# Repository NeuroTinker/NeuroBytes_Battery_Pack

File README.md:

# NeuroBytes Battery Pack

The NeuroBytes Battery Pack provides power to NeuroBytes products, open-source hardware neuron simulators designed and sold by [NeuroTinker, LLC](http://www.neurotinker.com/). Battery Packs feature a pair of power connections and a power switch with indicator LED, and require four alkaline AA batteries to operate.

These boards were designed in KiCad and Inkscape and are released under the terms of the Creative Commons Attribution-ShareAlike 4.0 license, available here: https://creativecommons.org/licenses/by-sa/4.0/. The NeuroBytes Battery Pack is Certified Open Source Hardware as defined by [OSHWA](https://www.oshwa.org), certification number US000114.

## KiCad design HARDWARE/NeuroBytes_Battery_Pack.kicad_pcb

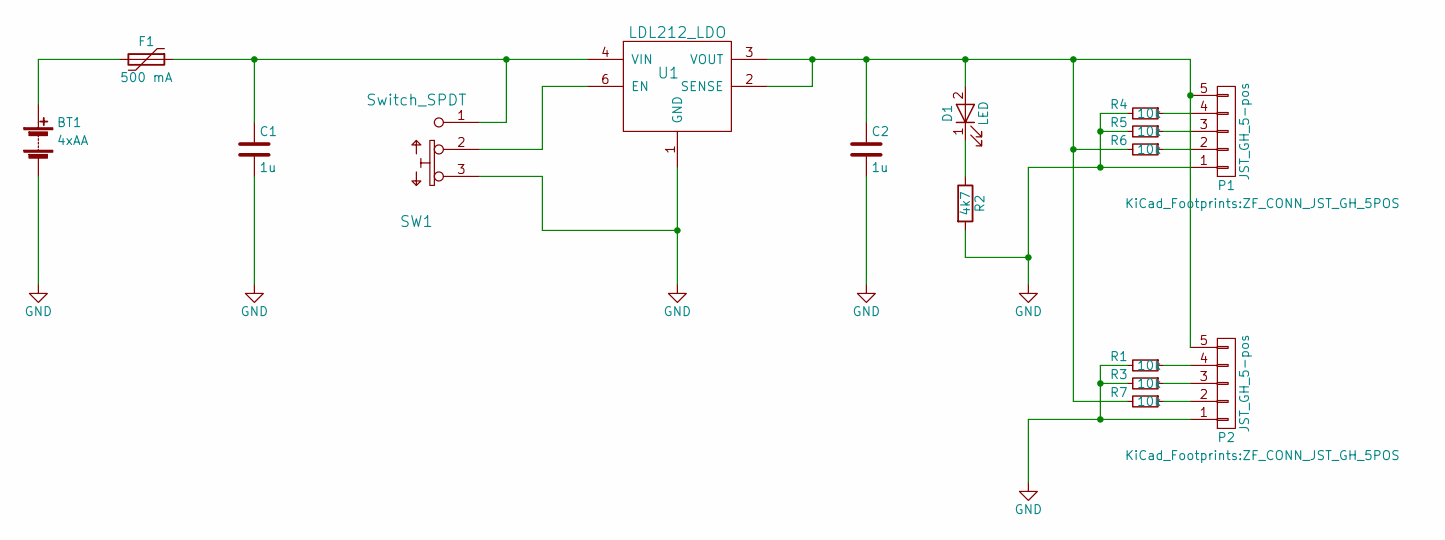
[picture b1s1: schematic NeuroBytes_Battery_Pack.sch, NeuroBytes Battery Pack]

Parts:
BT1: 4xAA; ZF_BATT_4xAA_BC4AAPC; Mfr Part # BC4AAPC
C1, C2: 1u; C_0603_HandSoldering; Mfr Part # LMK107B7105KA-T
D1: LED; ZF_SMD_NonPol_0402; Mfr Part # SMLP13EC8TT86
F1: 500 mA; ZF_SMD_nonpol_1210; Mfr Part # 0ZCH0050FF2G
P1, P2: JST_GH_5-pos; ZF_CONN_JST_GH_5POS; Mfr Part # SM05B-GHS-TB(LF)(SN)
R1, R3, R4, R5, R6, R7: 10k; ZF_SMD_NonPol_0402; Mfr Part # RC0402FR-0710KL
R2: 4k7; ZF_SMD_NonPol_0402; Mfr Part # RC0402FR-074K7L
SW1: Switch_SPDT; ZF_SW_PCM12SMTR; Mfr Part # PCM12SMTR
U1: LDL212_LDO; ZF_IC_DFN6_3x3; Mfr Part # LDL212PU50R

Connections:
GND: BT1.2 (-), C1.2, C2.2, P1.1, P2.1, R1.2, R2.2, R3.2, R4.2, R5.2, SW1.3, U1.1 (GND)
unnamed: BT1.1 (+), F1.2
unnamed: C1.1, F1.1, SW1.1, U1.4 (VIN)
unnamed: C2.1, D1.2 (A), P1.5, P2.5, R6.2, R7.2, U1.2 (SENSE), U1.3 (VOUT)
unnamed: D1.1 (K), R2.1
unnamed: P1.2, R6.1
unnamed: P1.3, R5.1
unnamed: P1.4, R4.1
unnamed: P2.2, R7.1
unnamed: P2.3, R3.1
unnamed: P2.4, R1.1
unnamed: SW1.2, U1.6 (EN)

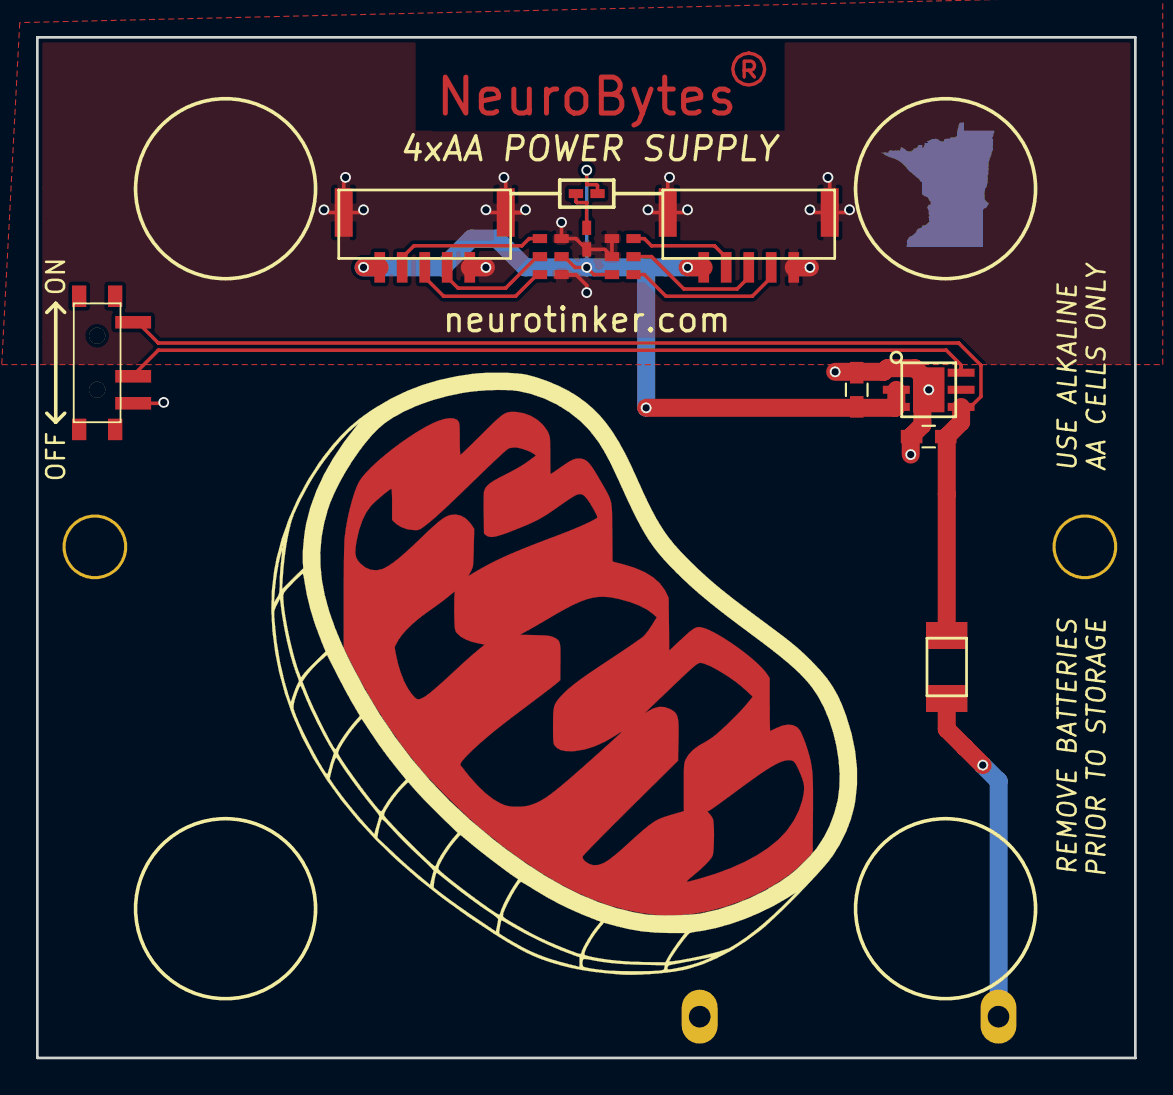
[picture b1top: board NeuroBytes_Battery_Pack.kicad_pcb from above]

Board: 2 copper layers, 61.0 x 56.7 mm, 16 parts (1 on the bottom side), 12 nets.

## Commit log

2017-08-29 pulled in battery pack design files from previous repo. 'first' commit.
2017-09-06 illustration updates
2017-09-06 fresh *.png exports
2017-09-06 update readme.md w/picture
2017-09-19 updated to include two 5-pin JST connectors and side-mtg switch. Moved LED to center.
2017-09-20 updated graphics to reflect new switch and dual-output PCB
2017-09-20 updated *.png exports to reflect new connector location and switch style
2017-10-04 updated component labels and regenerated netlist. generated BOM. minor page layout updates.
2017-11-29 updated license and readme. added drawing number and license to PCB layout drawing.
2018-03-08 added OSHWA logo and cert number
2018-03-08 README.md modification
2018-03-08 OSHWA img modification
2018-03-08 minor formatting updates
2018-03-08 minor README.md formatting updates
2018-03-08 minor README.md format updates
2018-03-08 minor img format update
2018-05-23 generated BOM and fab files
2018-05-23 updated INSERT attribute and regenerated position file
2018-05-31 updated schematic license and sheet size. added schematic pdf.
2018-07-20 added copper fill and via stitching around JST GH structural pads
2018-08-08 updated footprints to include outlines. re-generated Gerbers. added placement pdf.
2018-08-08 regen drill file

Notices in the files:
HARDWARE/NeuroBytes_Battery_Pack.kicad_pcb:
(C) 2017 Zach Fredin
License: CC-BY-SA 4.0
README.md:
CC BY-SA 4.0
